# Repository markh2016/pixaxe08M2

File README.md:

# pixaxe08M2

In answer  to Bryan Cairns of void void realms as promised
For other Facebook  users  I would  have included  this on twitter   but unfortunately twitter are a set of  power crazy loons  who don't appreciate decent input neither do they have a sense  of  which is their loss not mine 
Ive also put this together for others interested  in learning embedded technologies 
and its ideal  for  schools ,  colleges  and universities 
You will need Kicad installed  which can be  found  with most  distributions  of open-source  Linux operating systems 
You will also need to run the Gerber  plots yourself  but all  tutorials can be found on U tube relating to this 

Its an excellent opening for  many to start manufacturing from  home in any country of the world  of which  most of this  can be done  by hand so Ive  made this easy as I can for you  and at better quality than  Pic axe   supply this  very basic board and at fraction of  price 

Many of theses components you could  find from scrap eg the  connectors etc but most of these components can be found  online  via eBay  and other major suppliers  apart from the  08M2 cpu 

RS components or CPC supply these

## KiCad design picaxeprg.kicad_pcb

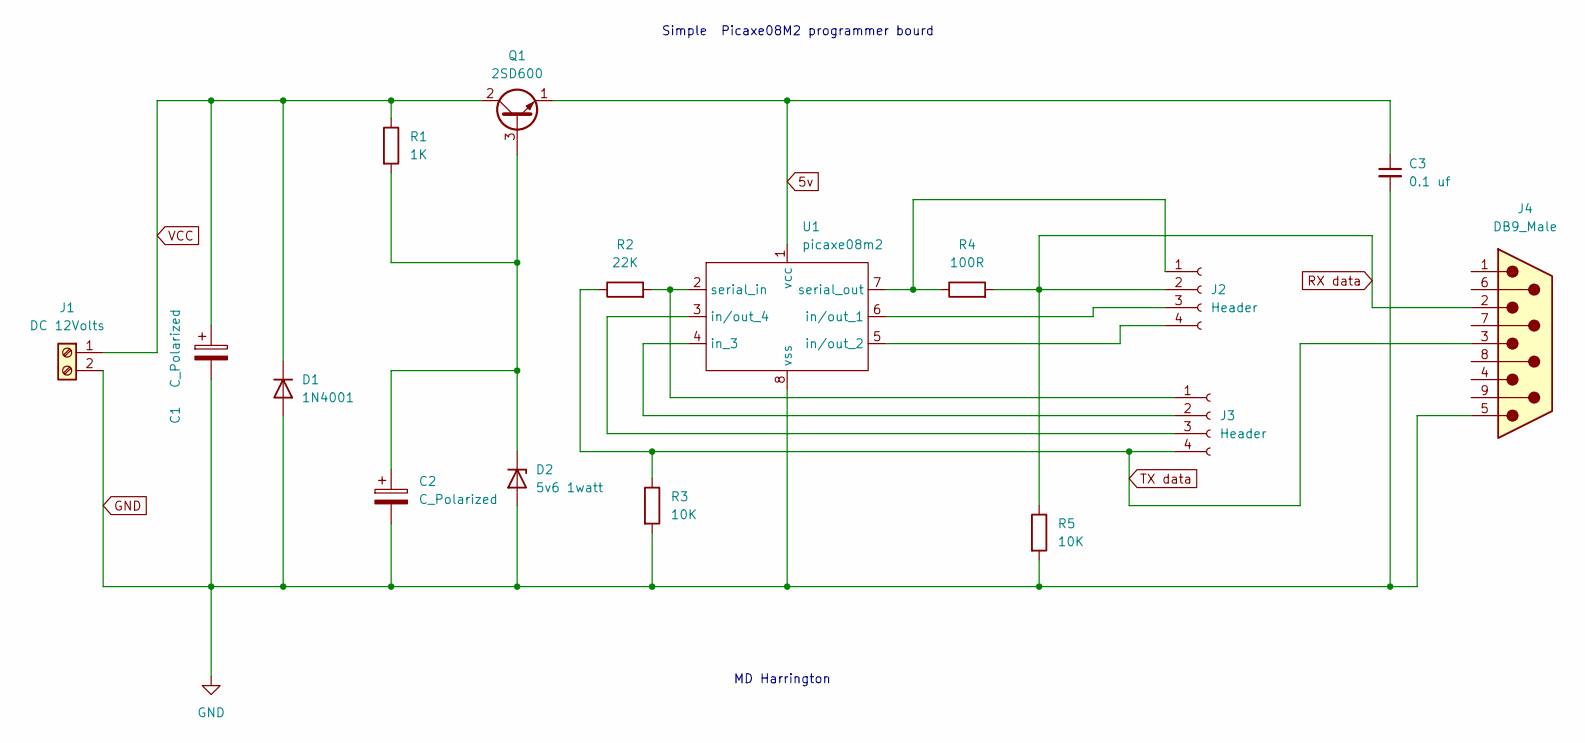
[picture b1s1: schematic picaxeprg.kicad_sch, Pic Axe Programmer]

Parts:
C1, C2: C_Polarized; CP_Radial_D6.3mm_P2.50mm
C3: 0.1 uf; C_Disc_D3.4mm_W2.1mm_P2.50mm
D1: 1N4001; D_DO-41_SOD81_P10.16mm_Horizontal
D2: 5v6 1watt; D_5W_P12.70mm_Horizontal
J1: DC 12Volts; TerminalBlock_MetzConnect_Type094_RT03502HBLU_1x02_P5.00mm_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
J2, J3: Header; Wuerth_WR-WTB_64800411622_1x04_P1.50mm_Vertical
J4: DB9_Male; DSUB-9_Female_Horizontal_P2.77x2.54mm_EdgePinOffset9.40mm
Q1: 2SD600; TO-126-3_Vertical
R1: 1K; R_Axial_DIN0207_L6.3mm_D2.5mm_P7.62mm_Horizontal
R2: 22K; R_Axial_DIN0207_L6.3mm_D2.5mm_P7.62mm_Horizontal
R3, R5: 10K; R_Axial_DIN0207_L6.3mm_D2.5mm_P7.62mm_Horizontal
R4: 100R; R_Axial_DIN0207_L6.3mm_D2.5mm_P7.62mm_Horizontal
U1: picaxe08m2; DIP-8_W7.62mm

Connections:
5v: C3.1, Q1.1 (E), U1.1 (vcc)
GND: C1.2, C2.2, C3.2, D1.2 (A), D2.2 (A), J1.2, J4.5, R3.2, R5.2, U1.8 (vss)
unnamed: C2.1, D2.1 (K), Q1.3 (B), R1.2
unnamed: J2.1, R4.1, U1.7 (serial_out)
unnamed: J2.3, U1.6 (in/out_1)
unnamed: J2.4, U1.5 (in/out_2)
unnamed: J3.1, R2.2, U1.2 (serial_in)
unnamed: J3.2, U1.4 (in_3)
unnamed: J3.3, U1.3 (in/out_4)
RX data: J2.2, J4.2, R4.2, R5.1
TX data: J3.4, J4.3, R2.1, R3.1
VCC: C1.1, D1.1 (K), J1.1, Q1.2 (C), R1.1

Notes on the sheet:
Simple Picaxe08M2 programmer bourd
MD Harrington

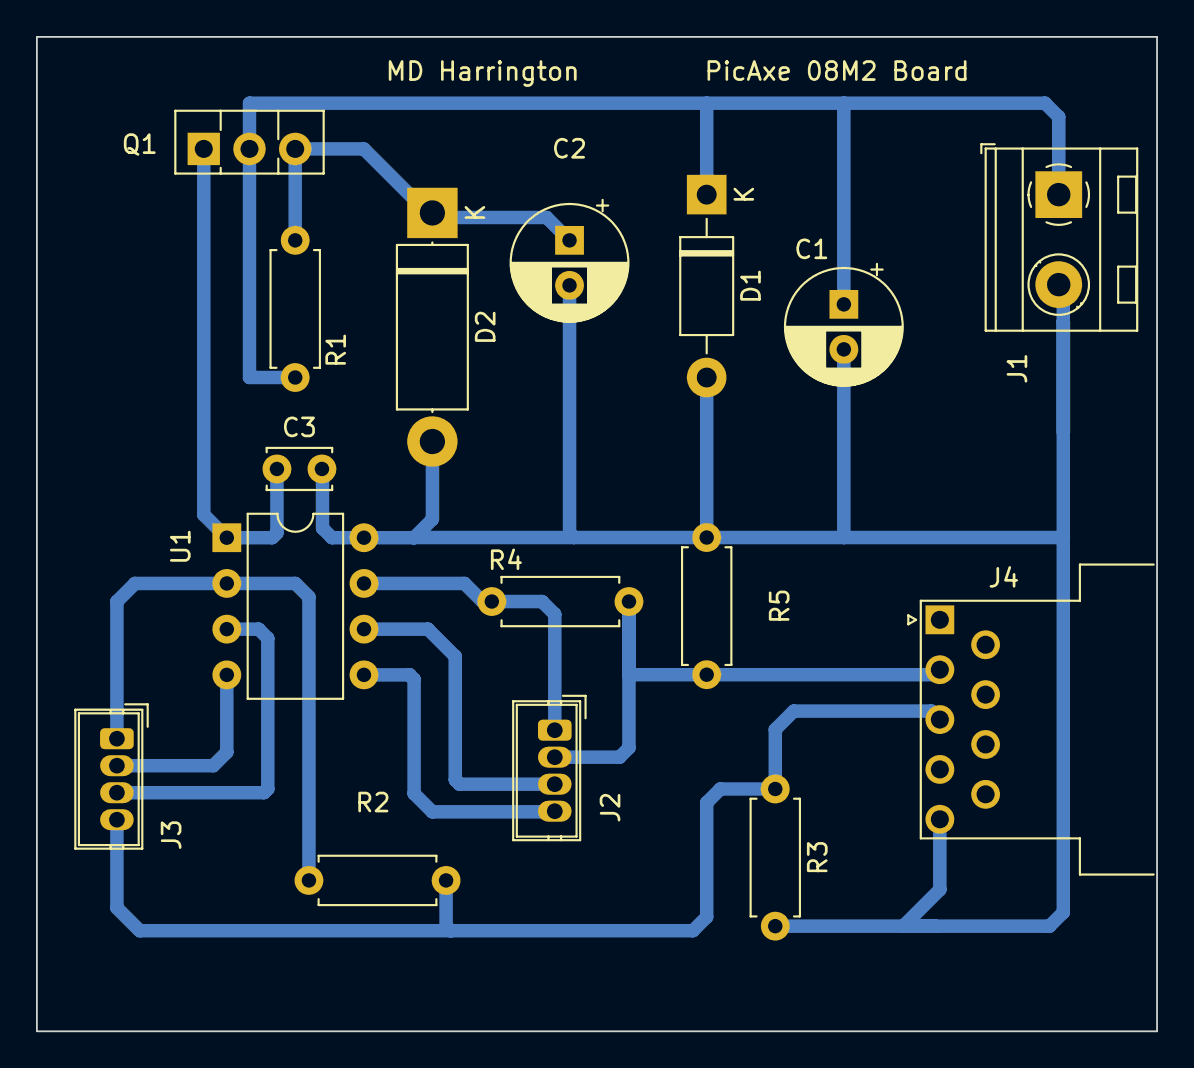
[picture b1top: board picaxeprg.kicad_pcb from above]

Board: 2 copper layers, 62.2 x 55.2 mm, 16 parts (0 on the bottom side), 12 nets.

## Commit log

2022-08-31 Add files via upload
    PicAxe 08M2 programmer board using Kicad for anyone interested in making these themselves
    Current price of these is some £19.39 without vat
2022-08-31 Add files via upload
    3D component view layout which should make this easier for others to build
2022-08-31 Add files via upload
    Parts listing showing you what you need
